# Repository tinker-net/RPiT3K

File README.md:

<div align="center">

# TON3K

**Neural Guitar Processing Platform**

Independent, open-source NAM guitar processor for dedicated hardware, Linux and desktop DAWs.

[Downloads](#downloads) · [Documentation](#documentation) · [Roadmap](docs/ROADMAP.md) · [Changelog](CHANGELOG.md)

</div>

---

## TON3K PiSound

A dedicated guitar rig for Raspberry Pi 5 and Blokas PiSound. Browser control, physical button gestures, optional hotspot, four presets and offline audio processing. Current PiSound source includes Practice Mode, smart NAM/IR library and offline backup. [Validation and rollback](docs/PROJECT_STATE.md). Published DEBs are older snapshots.

[Installation guide](README-PISOUND.md) · [Debian packages](https://github.com/tinker-net/RPiT3K/releases/tag/deb-preview-54)

## TON3K Standalone

A hardware-independent Linux guitar processor for ARM64 and x86-64, using configurable ALSA input/output. No PiSound driver, button or hotspot dependency. Raspberry Pi 4/5 and compatible 64-bit Linux systems. Experimental Cortex-A53 builds for Pi 3/3+ and Zero 2 W require community validation.

[Installation guide](README-GENERAL.md) · [Debian packages](https://github.com/tinker-net/RPiT3K/releases/tag/deb-preview-54)

## TON3K Native

The TON3K experience inside a DAW. VST3 for Windows, macOS and Linux; AU for macOS; LV2 for Linux. Native 0.1 was tested in Cubase on Apple Silicon; 0.2 is a development preview with successful CI builds, not yet host-validated.

[Plugin guide](vst3/README.md) · [Native downloads](#native-plugins)

---

**Shared direction:** one DSP core, consistent interface, shared library conventions and portable presets. Full convergence is a roadmap goal, not yet complete.

## Downloads

### Debian 13 / Raspberry Pi OS Trixie (64-bit)

The current published packages are experimental. Install only one variant; read the [package guide](packaging/README.md) before replacing an existing source installation.

| Edition | Target | Package |
| --- | --- | --- |
| PiSound | Pi 5 | [DEB](https://github.com/tinker-net/RPiT3K/releases/download/deb-preview-54/rpi-ton3k-pisound_0.1.0.preview54_arm64-cortex-a76.deb) |
| Standalone | Pi 5 | [DEB](https://github.com/tinker-net/RPiT3K/releases/download/deb-preview-54/rpi-ton3k_0.1.0.preview54_arm64-cortex-a76.deb) |
| Standalone | Pi 4 | [DEB](https://github.com/tinker-net/RPiT3K/releases/download/deb-preview-54/rpi-ton3k_0.1.0.preview54_arm64-cortex-a72.deb) |
| Standalone | ARM64 | [DEB](https://github.com/tinker-net/RPiT3K/releases/download/deb-preview-54/rpi-ton3k_0.1.0.preview54_arm64.deb) |
| Standalone | AMD64 | [DEB](https://github.com/tinker-net/RPiT3K/releases/download/deb-preview-54/rpi-ton3k_0.1.0.preview54_amd64.deb) |

[Release notes and SHA256 sums](https://github.com/tinker-net/RPiT3K/releases/tag/deb-preview-54)

### Native plugins

| System | Formats | Preview 0.2 CI artifact |
| --- | --- | --- |
| macOS Universal | VST3, AU | [ZIP](https://github.com/tinker-net/RPiT3K/actions/runs/45886130025/artifacts/15149044060) |
| Windows x64 | VST3 | [ZIP](https://github.com/tinker-net/RPiT3K/actions/runs/45886130025/artifacts/15149377294) |
| Linux x86-64 | VST3, LV2 | [ZIP](https://github.com/tinker-net/RPiT3K/actions/runs/45886130090/artifacts/15149417124) |
| Linux ARM64 | VST3, LV2 | [ZIP](https://github.com/tinker-net/RPiT3K/actions/runs/45886130090/artifacts/15150145838) |

These CI artifacts require GitHub login and expire. Native release publication is a separate manual promotion step after license compliance and host validation. macOS is ad-hoc signed, not notarized; AU registration is not yet confirmed. PiPedal does not automatically display the desktop LV2 editor.

## Experimental hardware support

| Edition | Target | Default backend | Hardware validation |
| --- | --- | --- | --- |
| PiSound | Pi 5 / Cortex-A76 | Embedded + NAM Core | Reference hardware; new DEB and Practice/GP acceptance pending |
| General | Pi 5 / Cortex-A76 | Embedded + NAM Core | Pending |
| General | Pi 4 / Cortex-A72 | NAM Core | Pending |
| General | Pi 3/3+ and Zero 2 W / Cortex-A53 | NAM Core | Community testing requested; maintainer will not test these targets |
| General | Portable ARM64 | NAM Core | Pending community validation |
| General | AMD64 / x86-64 | NAM Core | Maintainer intends to test later; no scheduled date |

The dedicated PiSound edition deliberately targets Pi 5 (and the installer permits Compute Module 5). Its A76 binary, fixed low-latency defaults and autonomous button/hotspot integration are not validated for Pi 4. This is a TON3K distribution/support decision, not an assertion that Blokas PiSound is incompatible with Pi 4. Pi 4 users may try the General A72 package with officially installed PiSound and configurable ALSA, without automatic PiSound button/hotspot provisioning. No 32-bit builds or original Pi Zero/Zero W support. Successful CI builds are not evidence of sustainable real-time performance on actual hardware. Pi 3/Zero 2 W validation is explicitly a community contribution, not a prerequisite for closing the Pi 5 edition.

[Unified experimental build workflow](https://github.com/tinker-net/RPiT3K/actions/workflows/pisound-experimental.yml). These builds are not the older published DEBs linked above.

## Documentation

- [PiSound](README-PISOUND.md)
- [Standalone](README-GENERAL.md)
- [Native plugins](vst3/README.md)
- [Debian packaging](packaging/README.md)
- [Architecture and source map](docs/ARCHITECTURE.md)
- [Roadmap](docs/ROADMAP.md)
- [Changelog](CHANGELOG.md)
- [Validation evidence](docs/PROJECT_STATE.md)
- [Historical source revisions](docs/SOURCE_HISTORY.md)

## Project status

PiSound is the reference hardware. The experimental unified DEBs share one source revision; published preview-54 packages remain older snapshots. Native shares DSP components but still has a separate chain implementation. No personal captures, API credentials or commercial IRs are distributed.

## Credits and licensing

Inspired by [TONE3000 × Daisy DIY Pedal](https://github.com/tone-3000/t3k-diy-pedal). This is an independent project, not an official TONE3000 product. Original firmware, hardware and companion are preserved for provenance; [upstream README](README-DAISY.md). See [LICENSE](LICENSE), [DaisySP notices](rpi/vendor/daisysp/README.md) and [artwork notice](UI-TONE3000-LICENSE.txt). Plugin redistribution requires review of JUCE and LGPL obligations. Capture and IR rights remain with their authors.

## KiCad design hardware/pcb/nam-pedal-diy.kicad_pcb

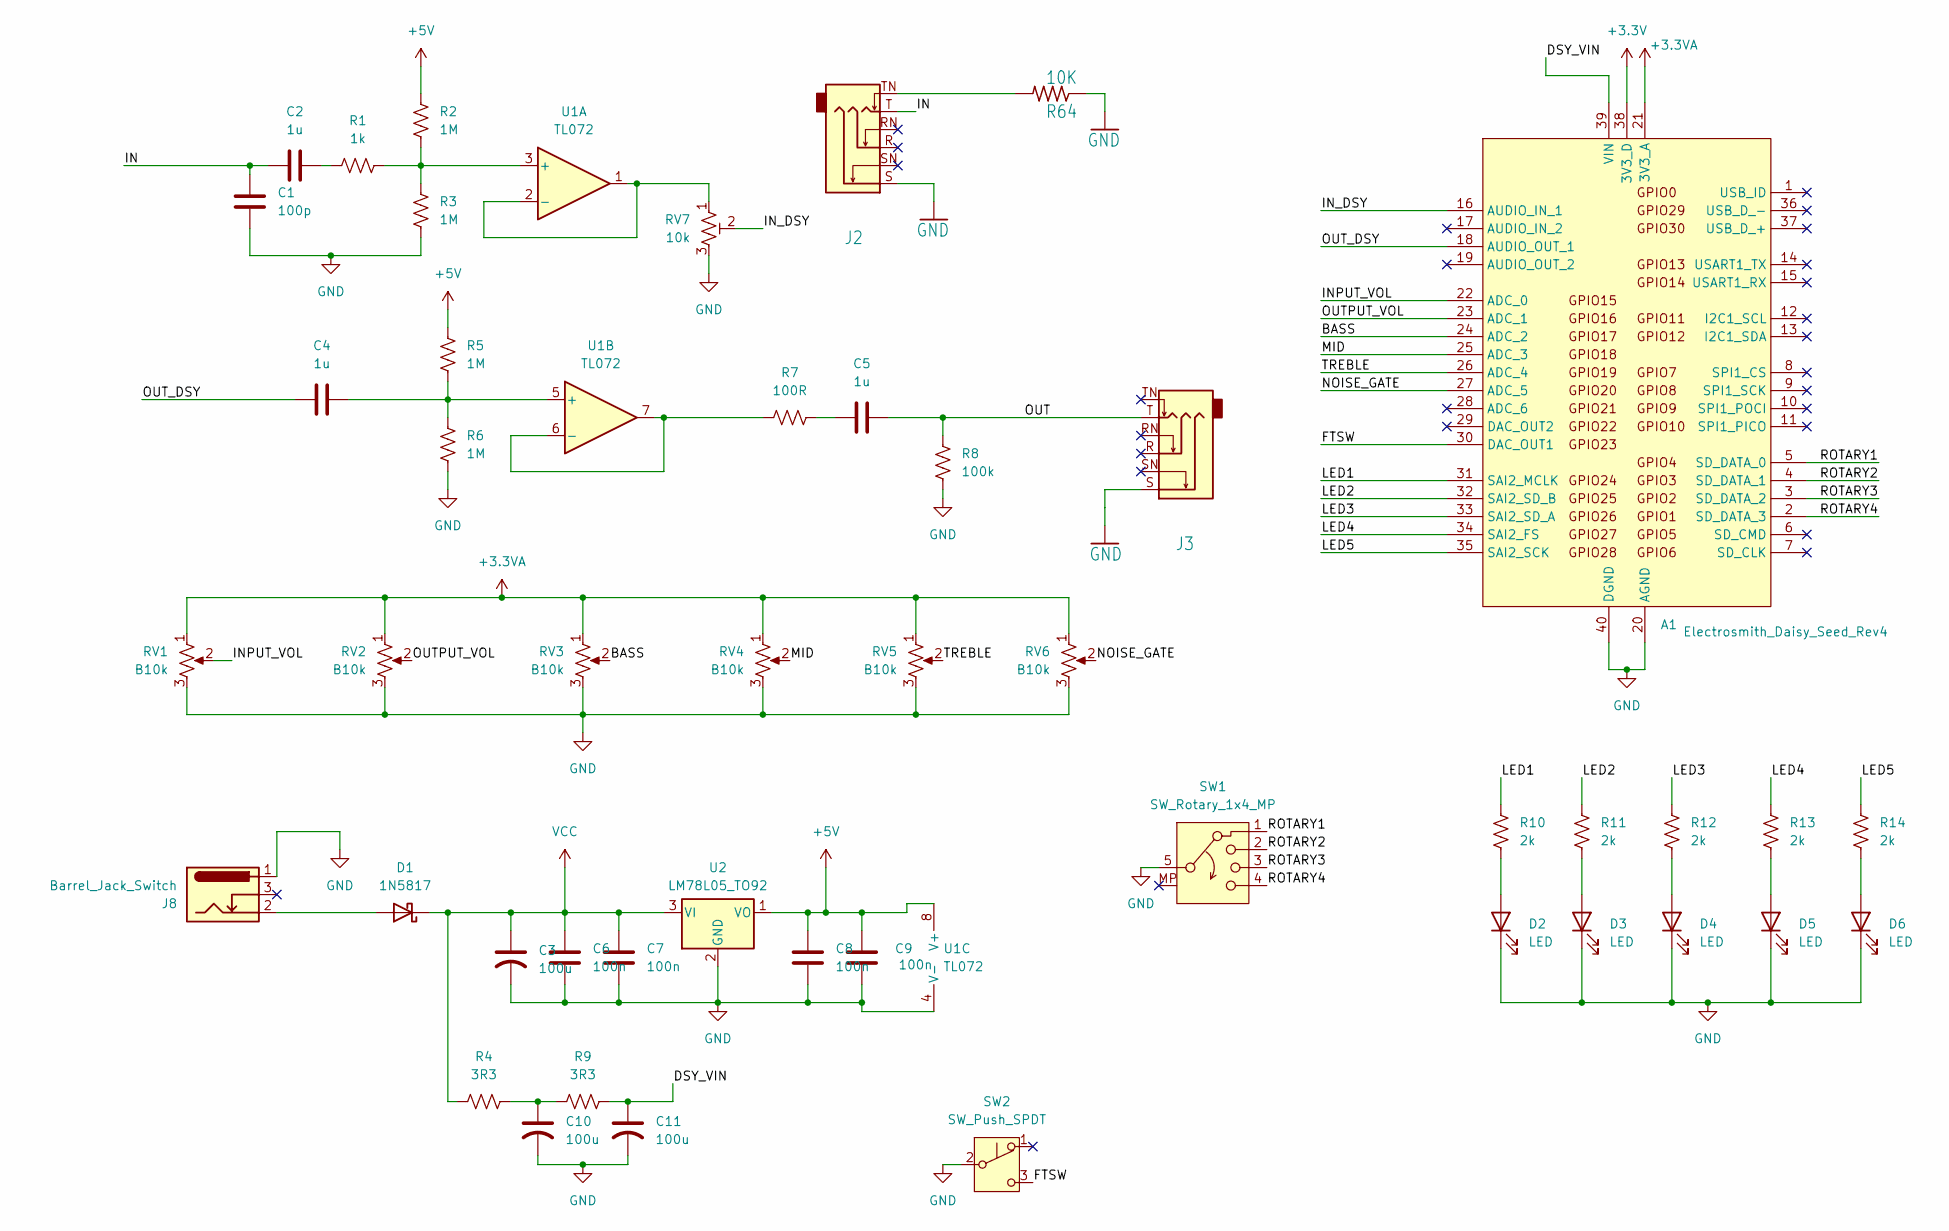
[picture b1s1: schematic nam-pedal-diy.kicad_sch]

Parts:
A1: Electrosmith_Daisy_Seed_Rev4; Electrosmith_Daisy_Seed
C1: 100p; C_Disc_D3.0mm_W1.6mm_P2.50mm
C2, C4, C5: 1u; C_Rect_L7.2mm_W6.0mm_P5.00mm
C3, C10, C11: 100u; CP_Radial_D5.0mm_P2.00mm
C6, C7, C8, C9: 100n; C_Rect_L7.2mm_W2.5mm_P5.00mm
D1: 1N5817; D_DO-41_SOD81_P10.16mm_Horizontal
D2, D3, D4, D5, D6: LED; LED_D3.0mm_reverse
J2: JACK_TRS_SWITCHING; 3T 6.35mm 14 Stereo Chassis Socket
J3: JACK_TRS_SWITCHING; 2T 6.35mm 14 Stereo Chassis Socket
J8: Barrel_Jack_Switch; 2 Pin DC Jack Chassis mount connector
R1: 1k; R_Axial_DIN0207_L6.3mm_D2.5mm_P7.62mm_Horizontal
R2, R3, R5, R6: 1M; R_Axial_DIN0207_L6.3mm_D2.5mm_P7.62mm_Horizontal
R4, R9: 3R3; R_Axial_DIN0207_L6.3mm_D2.5mm_P7.62mm_Horizontal
R7: 100R; R_Axial_DIN0207_L6.3mm_D2.5mm_P7.62mm_Horizontal
R8: 100k; R_Axial_DIN0207_L6.3mm_D2.5mm_P7.62mm_Horizontal
R10, R11, R12, R13, R14: 2k; R_Axial_DIN0207_L6.3mm_D2.5mm_P7.62mm_Horizontal
R64: 10K; R_Axial_DIN0207_L6.3mm_D2.5mm_P7.62mm_Horizontal
RV1, RV2, RV3, RV4, RV5, RV6: B10k; POT_16MM
RV7: 10k; Potentiometer_Runtron_RM-065_Vertical
SW1: SW_Rotary_1x4_MP; Rotary Switch 3 Pole 4 Position ALPHA SR2511F
SW2: SW_Push_SPDT; 2 Pin FTSW
U1: TL072; DIP-8_W7.62mm
U2: LM78L05_TO92; TO-92_Inline_Wide

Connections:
+3.3V: A1.38 (3V3_D)
+3.3VA: A1.21 (3V3_A), RV1.1, RV2.1, RV3.1, RV4.1, RV5.1, RV6.1
+5V: C8.2, C9.2, R2.1, R5.1, U1.8 (V+), U2.1 (VO)
/BASS: A1.24 (ADC_2), RV3.2
/DSY_VIN: A1.39 (VIN), C11.1, R9.2
/FTSW: A1.30 (DAC_OUT1), SW2.3 (C)
/IN: C1.1, C2.1, J2.T
/INPUT_VOL: A1.22 (ADC_0), RV1.2
/IN_DSY: A1.16 (AUDIO_IN_1), RV7.2
/LED1: A1.31 (SAI2_MCLK), R10.1
/LED2: A1.32 (SAI2_SD_B), R11.1
/LED3: A1.33 (SAI2_SD_A), R12.1
/LED4: A1.34 (SAI2_FS), R13.1
/LED5: A1.35 (SAI2_SCK), R14.1
/MID: A1.25 (ADC_3), RV4.2
/NOISE_GATE: A1.27 (ADC_5), RV6.2
/OUT: C5.2, J3.T, R8.1
/OUTPUT_VOL: A1.23 (ADC_1), RV2.2
/OUT_DSY: A1.18 (AUDIO_OUT_1), C4.1
/ROTARY1: A1.5 (SD_DATA_0), SW1.1
/ROTARY2: A1.4 (SD_DATA_1), SW1.2
/ROTARY3: A1.3 (SD_DATA_2), SW1.3
/ROTARY4: A1.2 (SD_DATA_3), SW1.4
/TREBLE: A1.26 (ADC_4), RV5.2
GND: A1.20 (AGND), A1.40 (DGND), C1.2, C3.2, C6.1, C7.1, C8.1, C9.1, C10.2, C11.2, D2.1 (K), D3.1 (K), D4.1 (K), D5.1 (K), D6.1 (K), J2.S, J3.S, J8.1, R3.2, R6.2, R8.2, R64.1, RV1.3, RV2.3, RV3.3, RV4.3, RV5.3, RV6.3, RV7.3, SW1.5, SW2.2 (B), U1.4 (V-), U2.2 (GND)
unnamed: C2.2, R1.1
unnamed: C5.1, R7.2
unnamed: C10.1, R4.2, R9.1
unnamed: D1.2 (A), J8.2
unnamed: D2.2 (A), R10.2
unnamed: D3.2 (A), R11.2
unnamed: D4.2 (A), R12.2
unnamed: D5.2 (A), R13.2
unnamed: D6.2 (A), R14.2
unnamed: J2.TN, R64.2
unnamed: R1.2, R2.2, R3.1, U1.3 (+)
unnamed: RV7.1, U1.1, U1.2 (-)
unnamed: C4.2, R5.2, R6.1, U1.5 (+)
unnamed: R7.1, U1.6 (-), U1.7
VCC: C3.1, C6.2, C7.2, D1.1 (K), R4.1, U2.3 (VI)

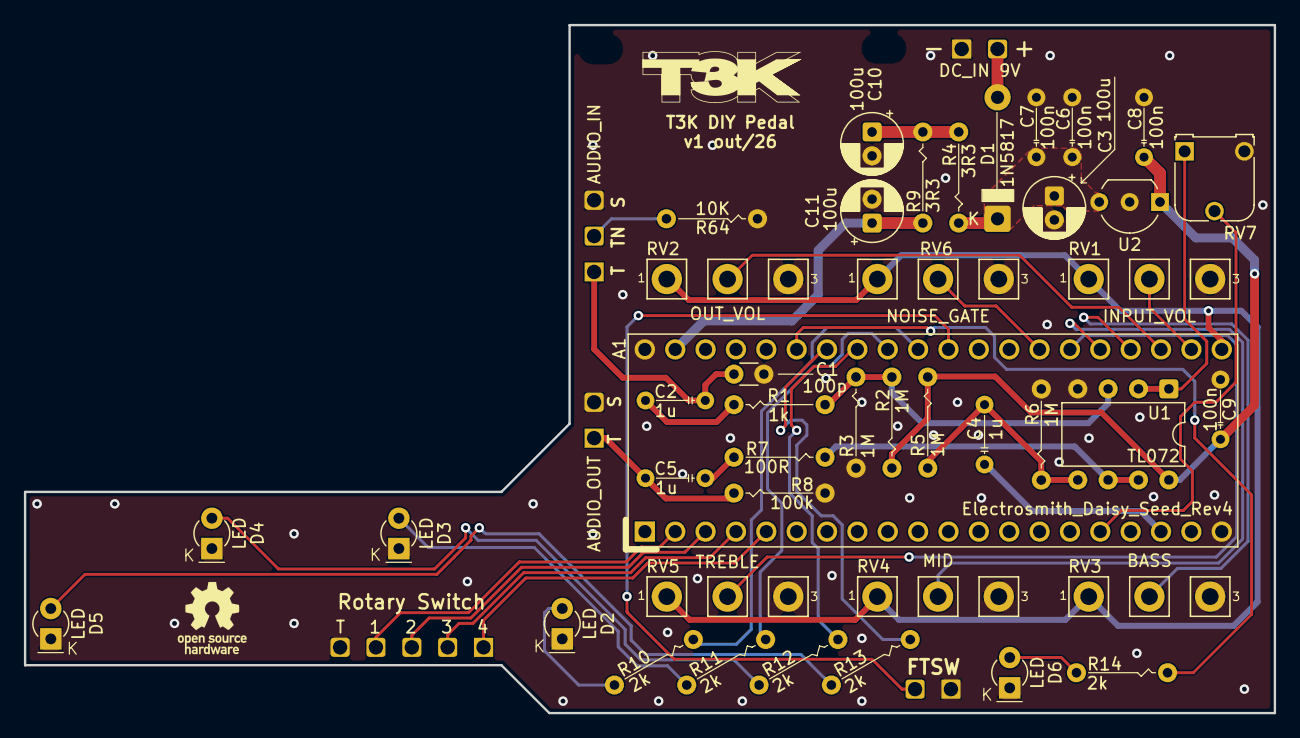
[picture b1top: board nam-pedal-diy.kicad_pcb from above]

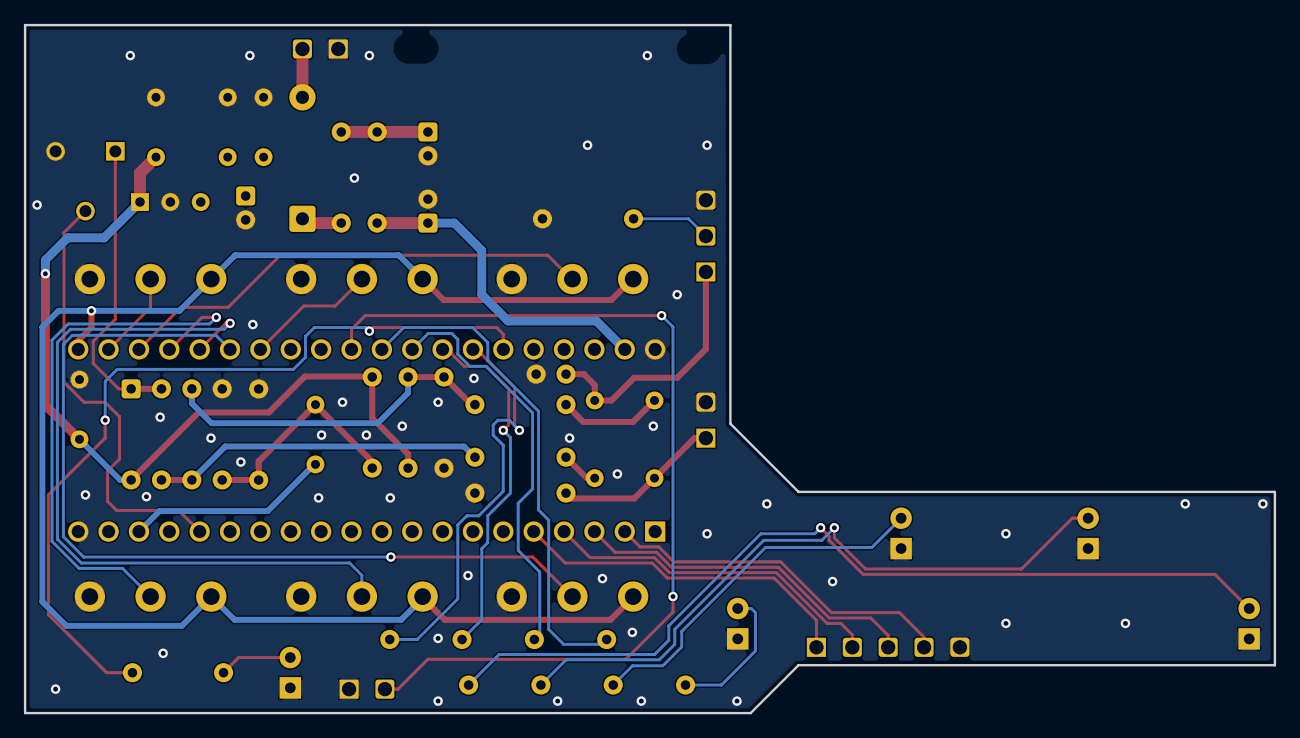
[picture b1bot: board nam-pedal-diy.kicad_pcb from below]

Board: 4 copper layers, 104.5 x 57.6 mm, 47 parts (6 on the bottom side), 39 nets.

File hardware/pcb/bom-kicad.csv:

"Reference","Value","Footprint","Qty"
"A1","Electrosmith_Daisy_Seed_Rev4","prj_lib:Electrosmith_Daisy_Seed","1"
"C1","100p","prj_lib:C_Disc_D3.0mm_W1.6mm_P2.50mm","1"
"C2,C4,C5","1u","prj_lib:C_Rect_L7.2mm_W6.0mm_P5.00mm","3"
"C3,C10,C11","100u","prj_lib:CP_Radial_D5.0mm_P2.00mm","3"
"C6-C9","100n","prj_lib:C_Rect_L7.2mm_W2.5mm_P5.00mm","4"
"D1","1N5817","prj_lib:D_DO-41_SOD81_P10.16mm_Horizontal","1"
"D2-D6","LED","prj_lib:LED_D3.0mm_reverse","5"
"J2","JACK_TRS_SWITCHING","prj_lib:3T 6.35mm 14 Stereo Chassis Socket","1"
"J3","JACK_TRS_SWITCHING","prj_lib:2T 6.35mm 14 Stereo Chassis Socket","1"
"J8","Barrel_Jack_Switch","prj_lib:2 Pin DC Jack Chassis mount connector","1"
"R1","1k","prj_lib:R_Axial_DIN0207_L6.3mm_D2.5mm_P7.62mm_Horizontal","1"
"R2,R3,R5,R6","1M","prj_lib:R_Axial_DIN0207_L6.3mm_D2.5mm_P7.62mm_Horizontal","4"
"R4,R9","3R3","prj_lib:R_Axial_DIN0207_L6.3mm_D2.5mm_P7.62mm_Horizontal","2"
"R7","100R","prj_lib:R_Axial_DIN0207_L6.3mm_D2.5mm_P7.62mm_Horizontal","1"
"R8","100k","prj_lib:R_Axial_DIN0207_L6.3mm_D2.5mm_P7.62mm_Horizontal","1"
"R10-R14","2k","prj_lib:R_Axial_DIN0207_L6.3mm_D2.5mm_P7.62mm_Horizontal","5"
"R64","10K","prj_lib:R_Axial_DIN0207_L6.3mm_D2.5mm_P7.62mm_Horizontal","1"
"RV1-RV6","B10k","prj_lib:POT_16MM","6"
"RV7","10k","Potentiometer_THT:Potentiometer_Runtron_RM-065_Vertical","1"
"SW1","SW_Rotary_1x4_MP","prj_lib:Rotary Switch 3 Pole 4 Position ALPHA SR2511F","1"
"SW2","SW_Push_SPDT","prj_lib:2 Pin FTSW","1"
"U1","TL072","prj_lib:DIP-8_W7.62mm","1"
"U2","LM78L05_TO92","prj_lib:TO-92_Inline_Wide","1"

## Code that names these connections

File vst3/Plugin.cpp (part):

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    nlohmann::json adcReference=nullptr, appearance=nlohmann::json::object();

    using Json=nlohmann::json;
    static constexpr const char* webKeys[]={"input","output","bass","mid","treble","gate","comp","comp_post","reverb","decay","reverb_type","ir_mix","hiz","hiz_profile","chorus","chorus_rate","chorus_depth","delay","delay_ms","delay_feedback"};
    void importFile(const juce::File& file){juce::Array<juce::File> a;a.add(file);importFiles(a);}
    Json webPreset(){
        Json j=Json::object();
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    juce::String status(){std::lock_guard<std::mutex> lock(configLock);return juce::String(supported.load()?juce::String(hostRate.load()/1000.,1)+" kHz | ":juce::String("Unsupported rate (dry bypass) | "))+message;}
    juce::String filename(int i){std::lock_guard<std::mutex> lock(configLock);return paths[i].isEmpty()?"Empty":juce::File(paths[i]).getFileName();}
private:
    static constexpr const char* ids[]={"input","output","bass","mid","treble","gate","comp","compPost","reverb","decay","reverbType","mix","hiz","profile","chorus","chorusRate","chorusDepth","delay","delayMs","feedback","stomp","amp","cab"};
    std::vector<std::atomic<float>*> params;
    float v(int i) const{return params[i]->load(std::memory_order_relaxed);}
    std::atomic<bool> supported{false};
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    std::unique_ptr<juce::FileChooser> chooser;
    int page=0;
    float inMeter=0,outMeter=0;
    static constexpr const char* ids[]={"input","output","bass","mid","treble","gate","comp","compPost","reverb","decay","reverbType","mix","hiz","profile","chorus","chorusRate","chorusDepth","delay","delayMs","feedback"};
    static constexpr const char* names[]={"INPUT","OUTPUT","BASS","MID","TREBLE","GATE","COMP","POSITION","REVERB","DECAY","TYPE","IR BLEND","HI-Z","PROFILE","CHORUS","RATE","DEPTH","DELAY","TIME","FEEDBACK"};
    static constexpr const char* switchIds[]={"stomp","amp","cab"};
    void toggle(int i){
        if(auto* q=p.state.getParameter(switchIds[i])){
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

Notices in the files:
vst3/Plugin.cpp:
SPDX-License-Identifier: MIT
